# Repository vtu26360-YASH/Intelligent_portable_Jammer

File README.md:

# Intelligent_portable_Jammer
Overview

The Intelligent Portable Jammer Using AI and IoT is an AI-powered wireless monitoring and adaptive signal management system designed to detect and analyze unauthorized wireless communication activities in restricted environments. The project focuses on monitoring Wi-Fi, Bluetooth, and mobile communication signals using Software Defined Radio (SDR), Artificial Intelligence, and IoT technologies.

The system continuously scans nearby RF signals, processes the collected data using machine learning algorithms, and provides real-time monitoring through an IoT dashboard. The project is designed with portability, low latency, and adaptive signal analysis capabilities for secure environments such as examination halls, secure facilities, and restricted zones.

Features:

Real-time Wi-Fi and Bluetooth signal detection.  

AI-based wireless signal classification.

FFT-based RF signal analysis.

IoT dashboard for live monitoring and alerts.

Portable and energy-efficient architecture.

Adaptive wireless monitoring using SDR technology.

Technologies Used:

NVIDIA Jetson Nano.
RTL-SDR.
HackRF One.
ESP32.
GNU Radio.
Python.
Garuda Linux.
Random Forest / CNN.
FFT (Fast Fourier Transform).

Project Workflow:

RF signals are captured using RTL-SDR and Wi-Fi adapters.
Signal data is processed using GNU Radio and FFT analysis.
Features such as RSSI, packet activity, and frequency patterns are extracted.
Machine learning algorithms classify authorized and unauthorized activities.
Real-time monitoring and alerts are displayed through the IoT dashboard.
Examination Hall Monitoring.
Restricted Area Security.
Wireless Activity Monitoring.
IoT-based RF Signal Analysis.
Research in AI-based SDR Systems.
Future Enhancements.
Support for advanced 5G signal analysis.
CNN-based deep learning classification.
Mobile application for remote monitoring.
Improved adaptive response mechanisms.
Cloud-based analytics and monitoring team.

Developed as a Minor Project in the Department of Computer Science & Engineering (Cyber Security).

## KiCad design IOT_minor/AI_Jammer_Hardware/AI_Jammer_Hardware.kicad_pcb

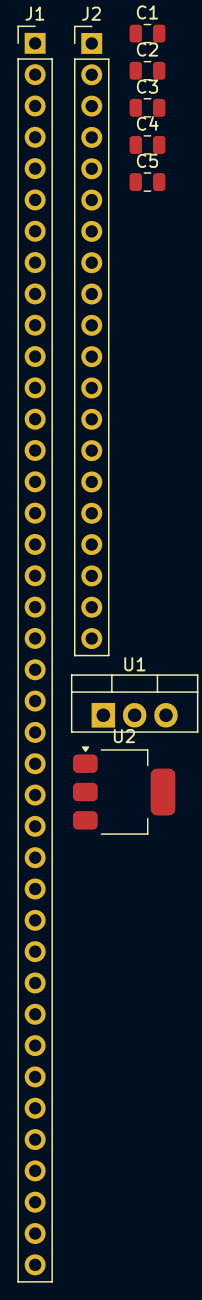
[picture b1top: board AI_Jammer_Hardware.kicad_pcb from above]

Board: 2 copper layers, 9 parts (0 on the bottom side), 3 nets, no tracks yet.

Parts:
C1, C2, C3, C4, C5: 100nF; C_0805_2012Metric
J1: Conn_01x40_Pin; PinHeader_1x40_P2.54mm_Vertical
J2: Conn_01x20_Pin; PinHeader_1x20_P2.54mm_Vertical
U1: LM7805_TO220; TO-220-3_Vertical
U2: AMS1117-3.3; SOT-223-3_TabPin2

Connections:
3V3: C1.1, C2.1, C3.1, C4.1, C5.1, J2.1
5V: J1.2, J1.4, U2.3
GND: C1.2, C2.2, C3.2, C4.2, C5.2, J1.6, J1.9, J1.14, J1.20, J1.25, J1.30, J1.34, J1.39, J2.2, U2.1
